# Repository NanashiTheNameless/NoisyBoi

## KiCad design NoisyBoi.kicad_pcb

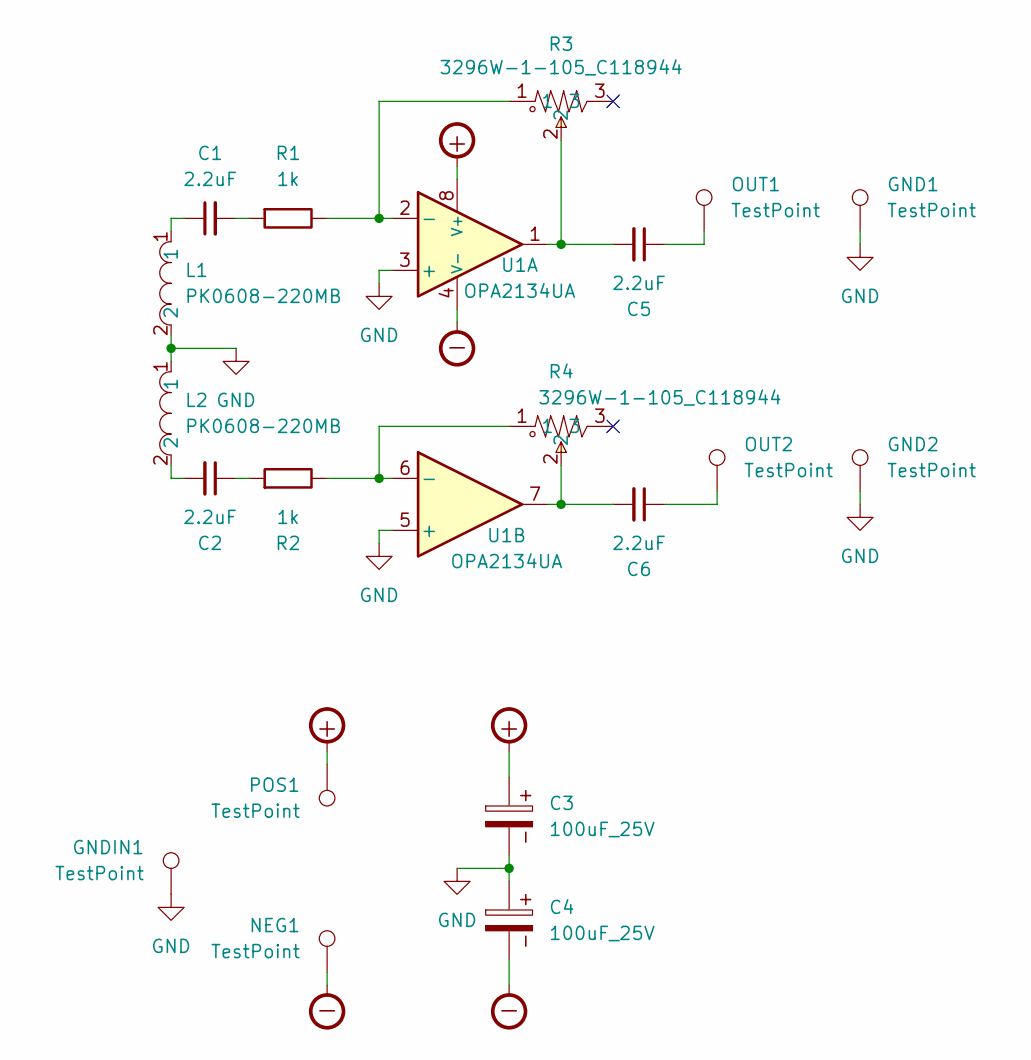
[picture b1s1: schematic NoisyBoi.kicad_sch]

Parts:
C1, C2, C5, C6: 2.2uF_0603_25V; C_Disc_D3.0mm_W1.6mm_P2.50mm; Part Number GRM188R6YA225KA12D; JLCPCB ID C57895
C3, C4: 100uF_25V; CP_Radial_D6.3mm_P2.50mm
GND1, GND2: TestPoint; Pin_D1.3mm_L11.0mm_LooseFit
GNDIN1: TestPoint; Pin_D1.3mm_L11.0mm_LooseFit
L1, L2: PK0608-220MB; IND-TH_BD7.0-P2.50-D0.7; LCSC Part C400298
NEG1: TestPoint; Pin_D1.3mm_L11.0mm_LooseFit
OUT1, OUT2: TestPoint; Pin_D1.3mm_L11.0mm_LooseFit
POS1: TestPoint; Pin_D1.3mm_L11.0mm_LooseFit
R1, R2: 1k; R_Axial_DIN0207_L6.3mm_D2.5mm_P10.16mm_Horizontal
R3, R4: 3296W-1-105_C118944; RES-ADJ-TH_3P-L10.0-W10.0-P2.50-BL-BS; LCSC Part C118944
U1: OPA2134UA; SO-8_3.9x4.9mm_P1.27mm

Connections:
GND: C3.2, C4.1, GND1.1, GND2.1, GNDIN1.1, L1.2, L2.1, U1.3 (+), U1.5 (+)
unnamed: C1.1, L1.1
unnamed: C1.2, R1.1
unnamed: C2.1, R2.1
unnamed: C2.2, L2.2
unnamed: C5.1, OUT1.1
unnamed: C5.2, R3.2, U1.1
unnamed: C6.1, OUT2.1
unnamed: C6.2, R4.2, U1.7
unnamed: R1.2, R3.1, U1.2 (-)
unnamed: R2.2, R4.1, U1.6 (-)
V-+: C3.1, POS1.1, U1.8 (V+)
V--: C4.2, NEG1.1, U1.4 (V-)

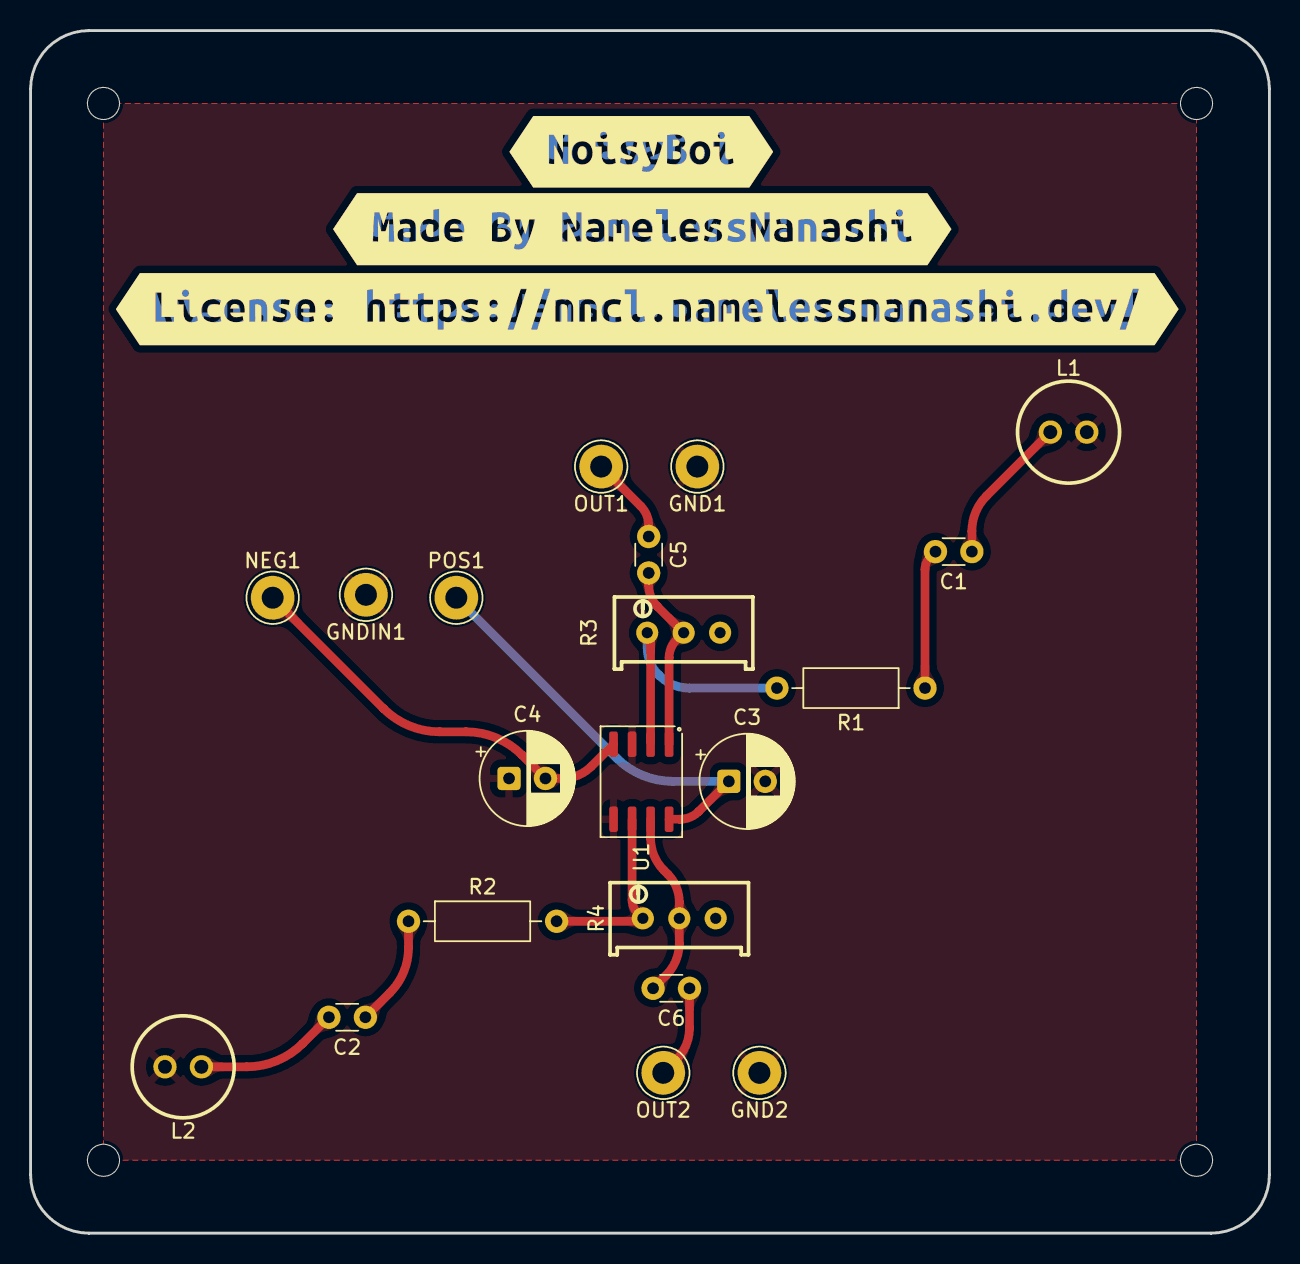
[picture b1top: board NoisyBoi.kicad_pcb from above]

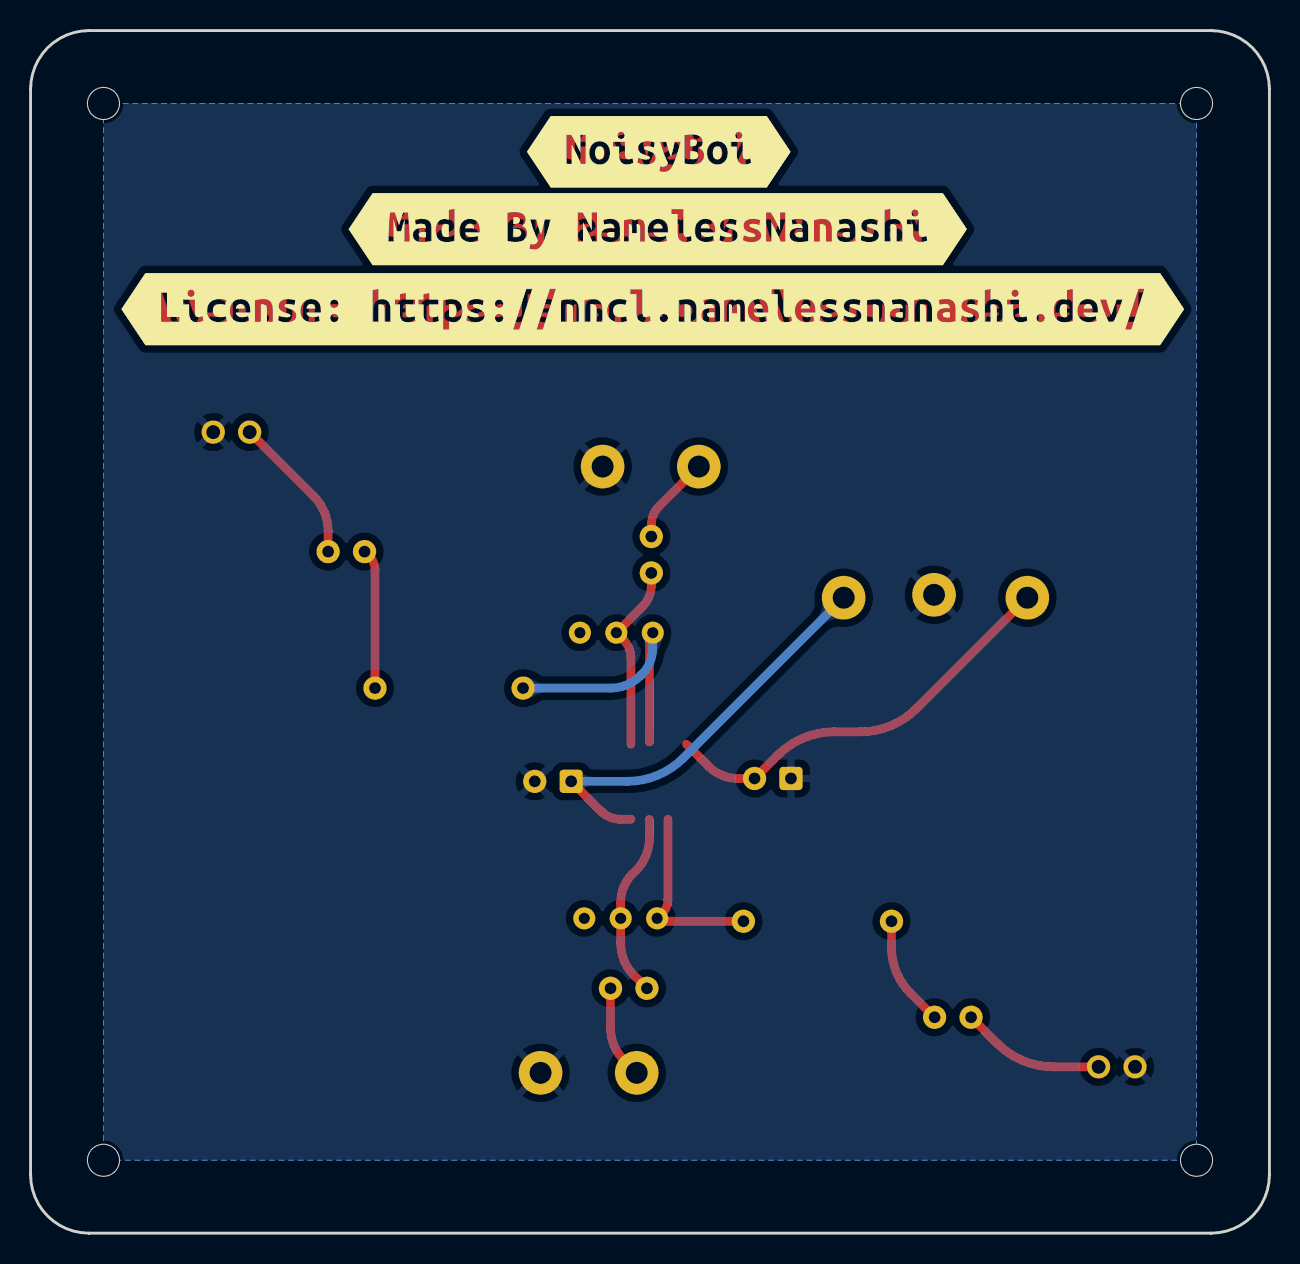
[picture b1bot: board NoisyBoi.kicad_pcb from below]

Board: 2 copper layers, 85.0 x 82.5 mm, 36 parts (6 on the bottom side), 13 nets.

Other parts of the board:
MPBL1: MountingHole_2.2mm_M2
MPBR1: MountingHole_2.2mm_M2
MPTL1: MountingHole_2.2mm_M2
MPTR1: MountingHole_2.2mm_M2
kibuzzard-691D6DA0: G***; kibuzzard-691D6DA0
kibuzzard-691D6DA7: G***; kibuzzard-691D6DA7
kibuzzard-691D6DFD: G***; kibuzzard-691D6DFD
kibuzzard-691D6E02: G***; kibuzzard-691D6E02
kibuzzard-691D639E, kibuzzard-691D639E#2: G***; kibuzzard-691D639E
kibuzzard-691D6368, kibuzzard-691D6368#2: G***; kibuzzard-691D6368
kibuzzard-691D6378, kibuzzard-691D6378#2: G***; kibuzzard-691D6378
kibuzzard-691D6399, kibuzzard-691D6399#2: G***; kibuzzard-691D6399

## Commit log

2025-11-19 Add LICENSE.md
2025-11-19 Add initial version
2025-11-19 fix typo (damnit)
